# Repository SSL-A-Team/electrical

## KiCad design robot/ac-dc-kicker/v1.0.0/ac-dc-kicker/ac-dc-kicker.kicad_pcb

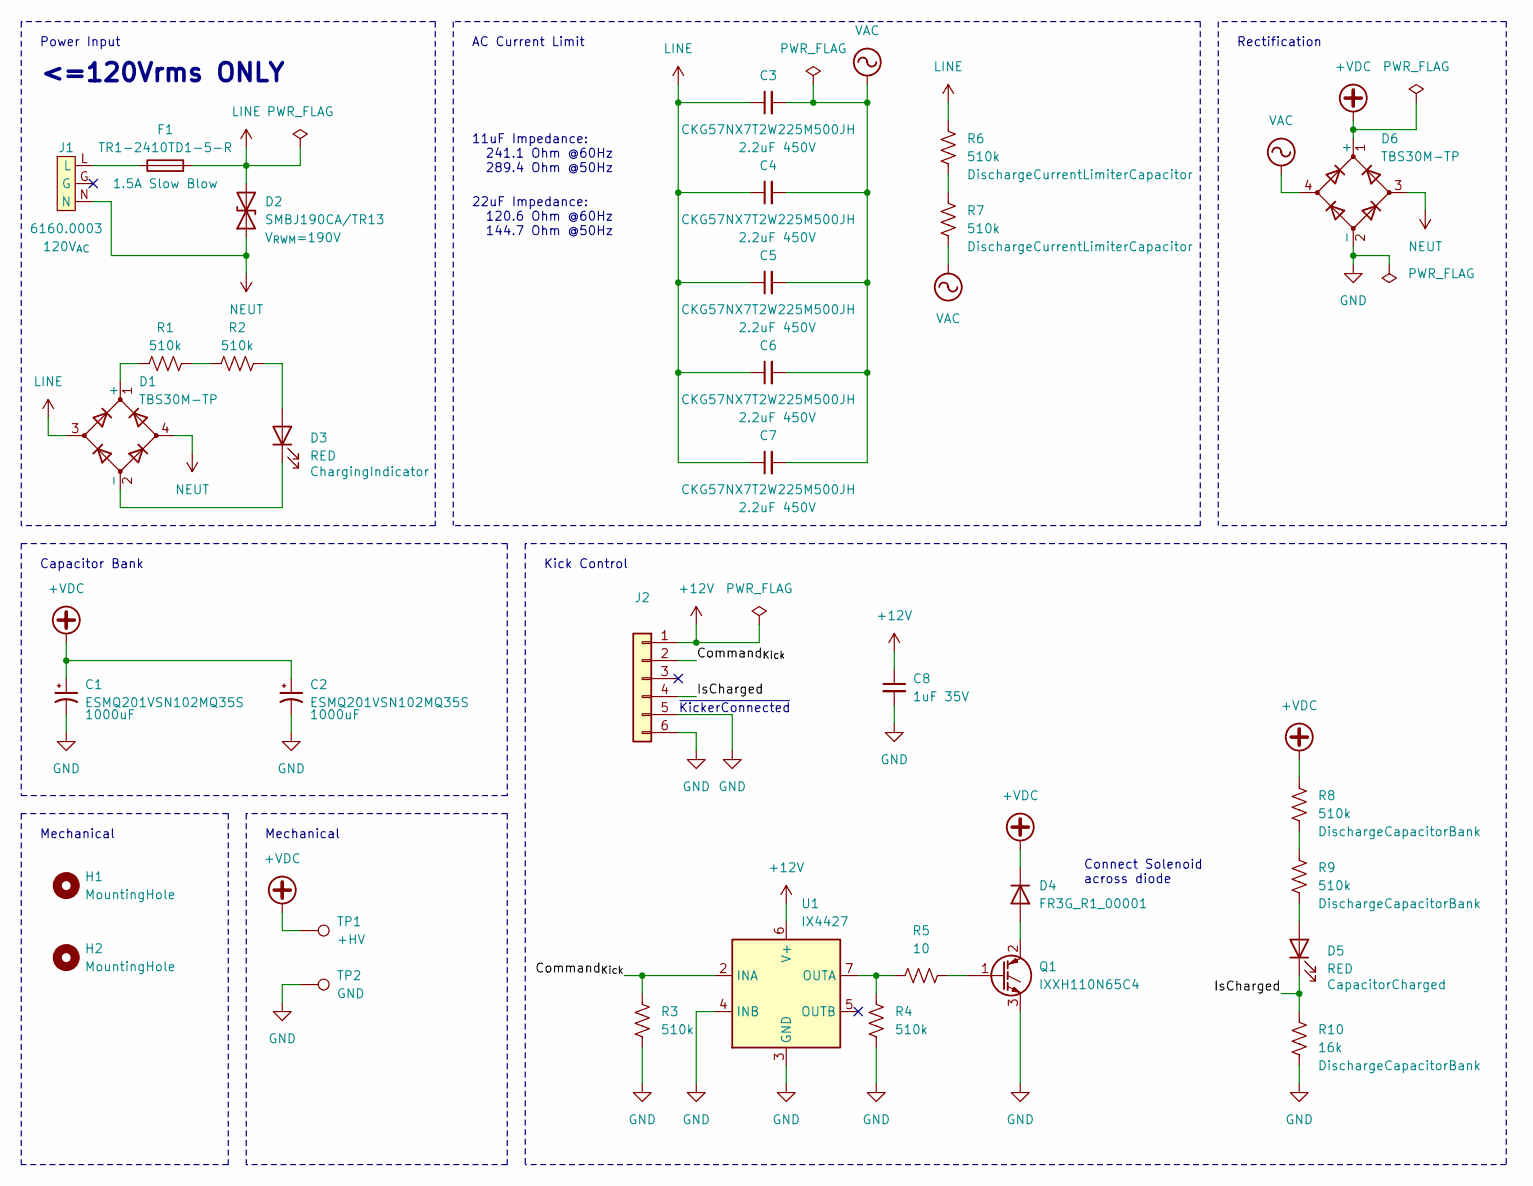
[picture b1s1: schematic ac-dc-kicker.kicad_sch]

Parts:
C1, C2: ESMQ201VSN102MQ35S; CP_Radial_D25.40mm_P10.00mm
C3, C4, C5, C6, C7: CKG57NX7T2W225M500JH; CKG57N
C8: 1uF 35V; LED_0603_1608Metric
D1, D6: TBS30M-TP; TBS
D2: SMBJ190CA/TR13; D_SMB_Non-Polar
D3, D5: RED; LED_0603_1608Metric
D4: FR3G_R1_00001; D_SMC
F1: TR1-2410TD1-5-R; Fuse_2410_6125Metric
H1, H2: MountingHole; MountingHole_3.2mm_M3
J1: 6160.0003
J2: 1x06_P2.5mm_ID0.8mm_OD2mm_TH
Q1: IXXH110N65C4; TO-247-3_Vertical
R1, R2, R3, R4, R6, R7, R8, R9: 510k; R_0805_2012Metric
R5: 10; R_0603_1608Metric
R10: 16k; R_0805_2012Metric
TP1: +HV; TestPoint_THTPad_D2.0mm_Drill1.0mm
TP2: GND; TestPoint_THTPad_D2.0mm_Drill1.0mm
U1: IX4427; SOIC-8_3.9x4.9mm_P1.27mm

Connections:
+12V: C8.1, J2.1, U1.6 (V+)
+VDC: C1.1, C2.1, D4.1 (K), D6.1 (+), R8.1, TP1.1
/Command_{Kick}: J2.2, R3.1, U1.2 (INA)
/IsCharged: D5.1 (K), J2.4, R10.1
GND: C1.2, C2.2, C8.2, D6.2 (-), J2.5, J2.6, Q1.3 (E), R3.2, R4.2, R10.2, TP2.1, U1.3 (GND), U1.4 (INB)
LINE: C3.1, C4.1, C5.1, C6.1, C7.1, D1.3, D2.2 (A2), F1.2, R6.1
NEUT: D1.4, D2.1 (A1), D6.3, J1.N
unnamed: D1.1 (+), R1.1
unnamed: D1.2 (-), D3.1 (K)
unnamed: D3.2 (A), R2.2
unnamed: D4.2 (A), Q1.2 (C)
unnamed: D5.2 (A), R9.2
unnamed: F1.1, J1.L
unnamed: Q1.1 (G), R5.2
unnamed: R1.2, R2.1
unnamed: R4.1, R5.1, U1.7 (OUTA)
unnamed: R6.2, R7.1
unnamed: R8.2, R9.1
VAC: C3.2, C4.2, C5.2, C6.2, C7.2, D6.4, R7.2

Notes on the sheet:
AC Current Limit
Power Input
<=120Vrms ONLY
Capacitor Bank
Rectification
Connect Solenoid across diode
Mechanical
22uF Impedance: 120.6 Ohm @60Hz 144.7 Ohm @50Hz
11uF Impedance: 241.1 Ohm @60Hz 289.4 Ohm @50Hz
Kick Control
~{KickerConnected}

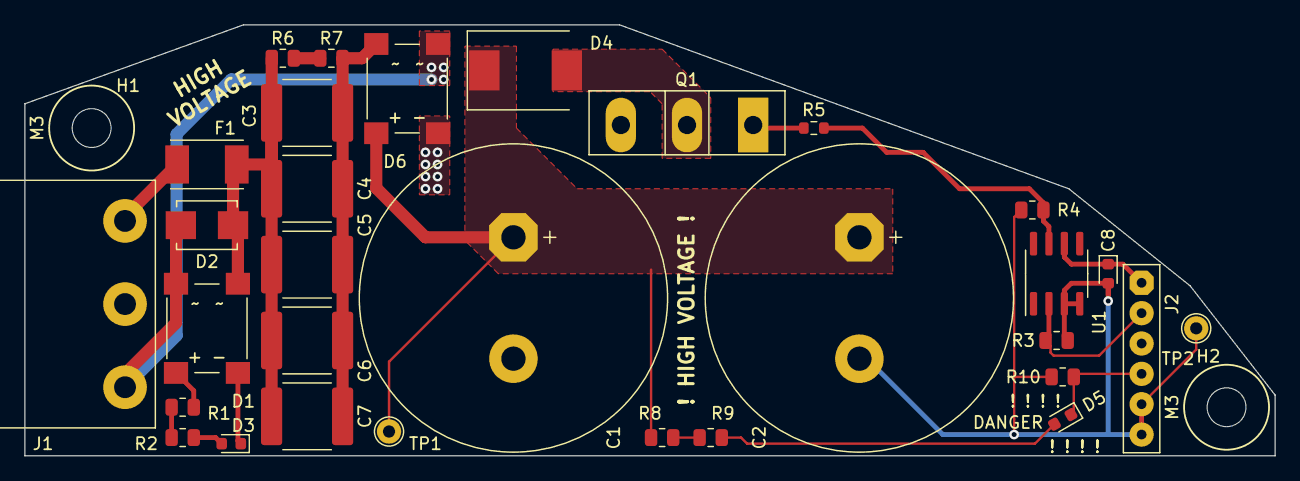
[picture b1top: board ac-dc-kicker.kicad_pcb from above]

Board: 2 copper layers, 103.0 x 35.5 mm, 33 parts (0 on the bottom side), 19 nets.

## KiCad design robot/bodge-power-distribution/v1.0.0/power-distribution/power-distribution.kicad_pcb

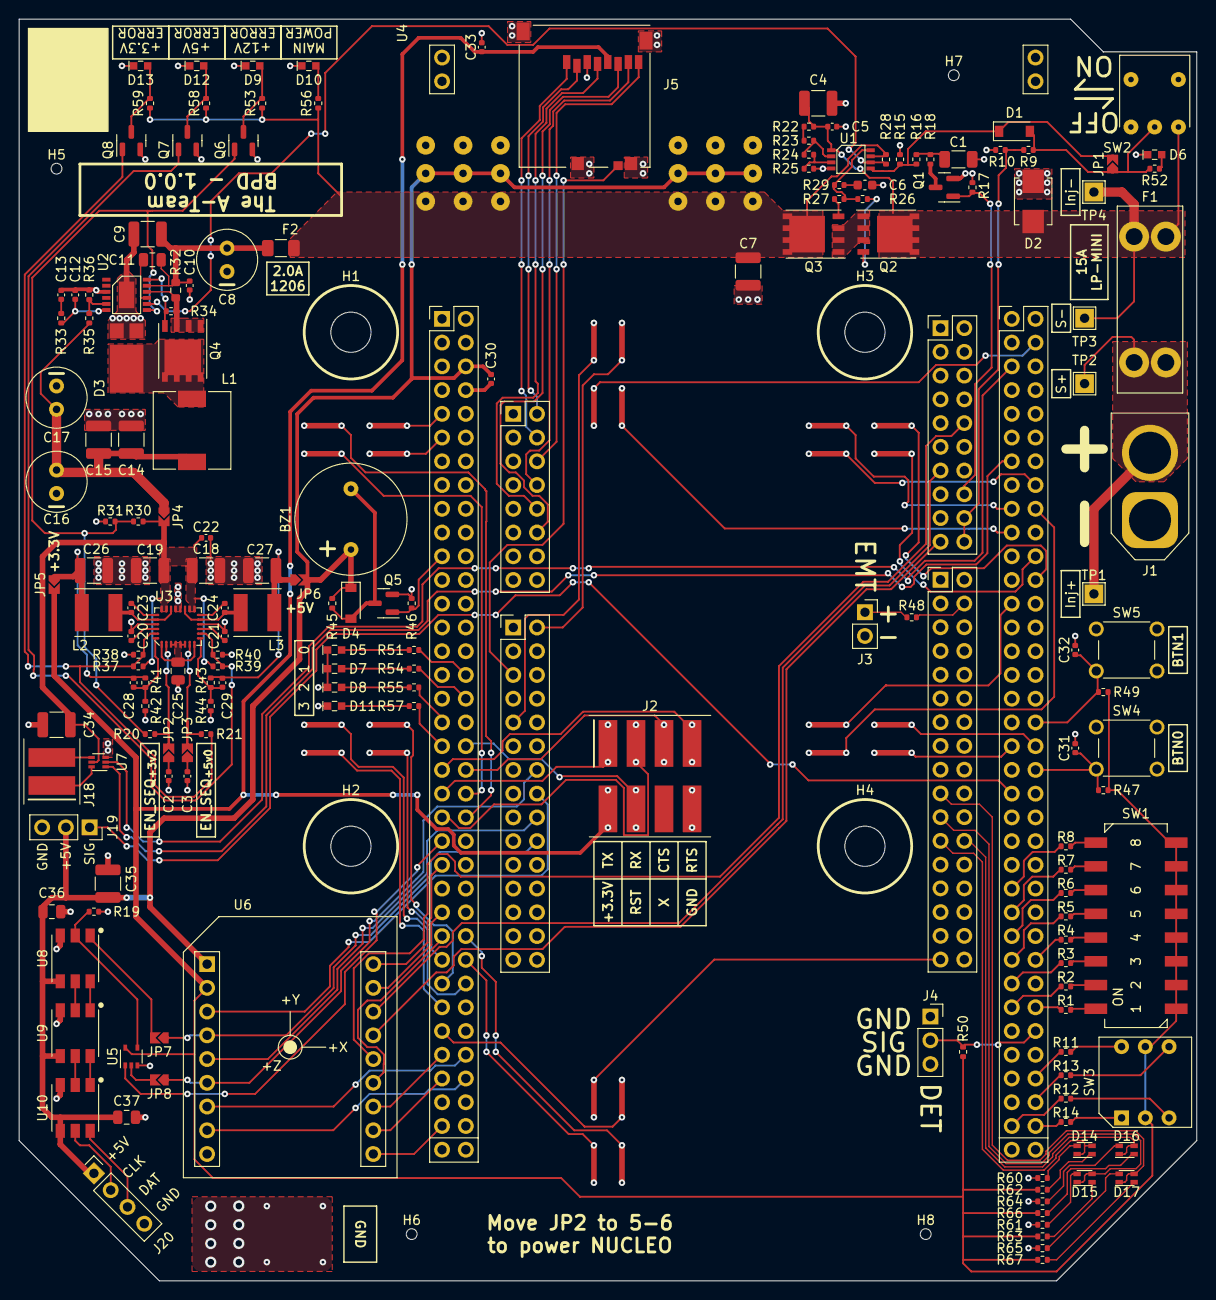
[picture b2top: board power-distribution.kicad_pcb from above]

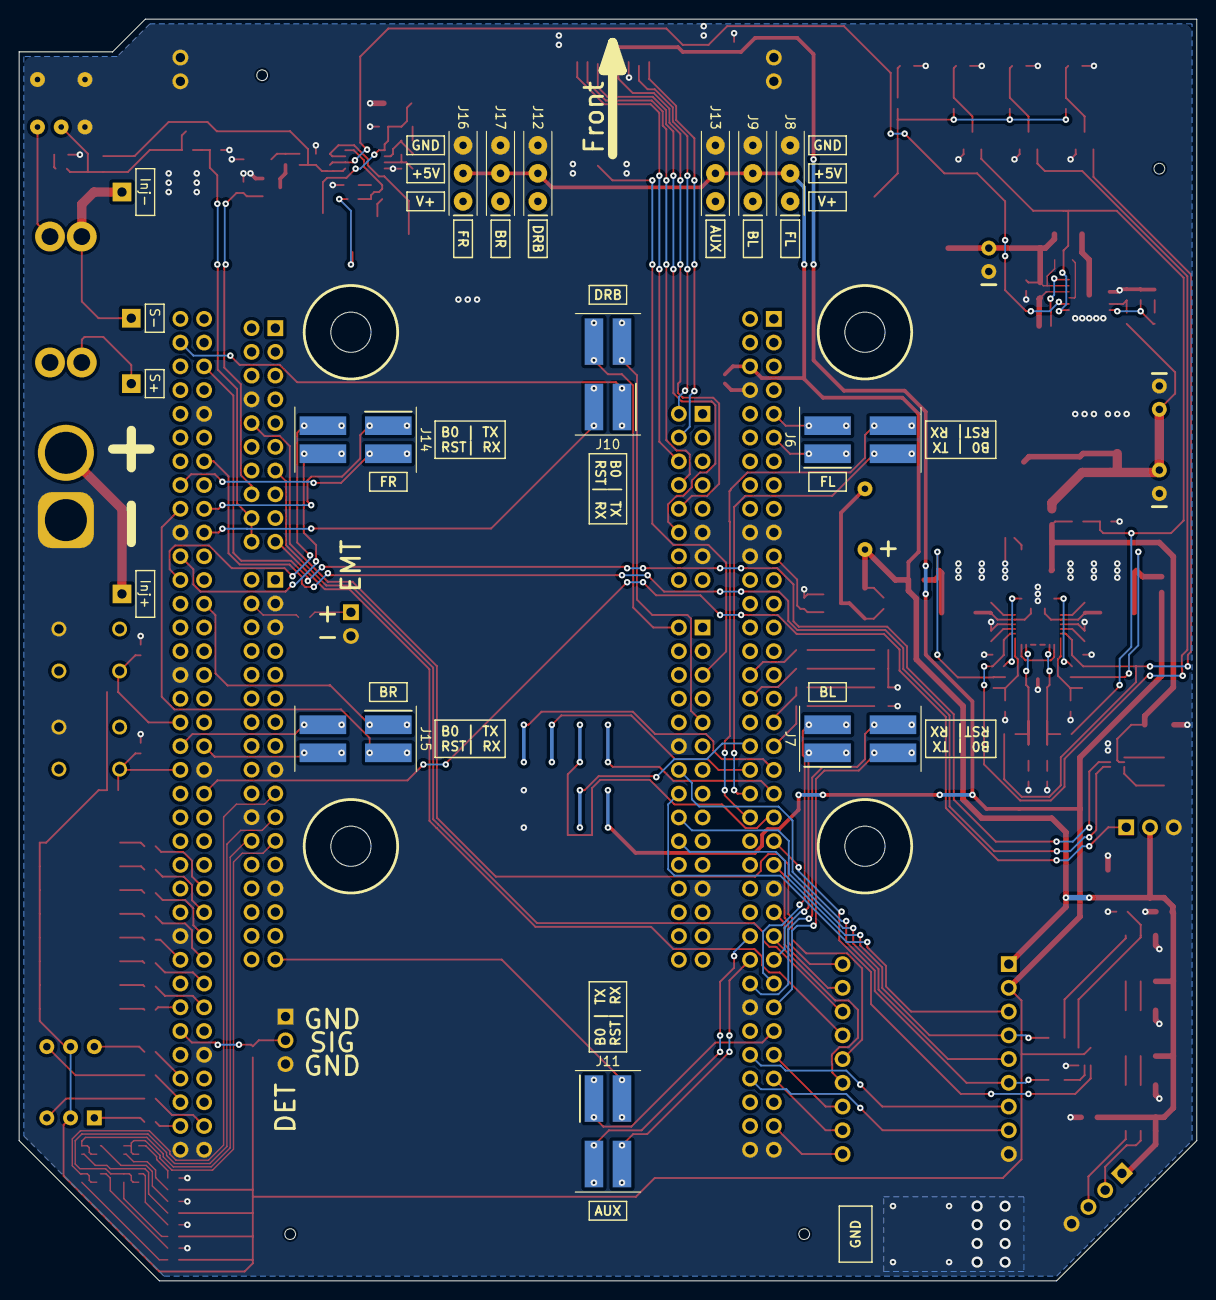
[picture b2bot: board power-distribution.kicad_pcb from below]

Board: 2 copper layers, 126.0 x 135.0 mm, 190 parts (12 on the bottom side), 171 nets.

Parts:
BZ1: AT-1224-TWT-5V-2-R
C1: 0.82uF 63V; C_1206_3216Metric
C2, C3, C5, C10, C20, C21, C22, C23, C24, C30, C31, C32, C33: 0.1uF 63V; C_0402_1005Metric
C4, C7, C9, C14, C15, C34, C35: 10uF 63V; C_1210_3225Metric
C6: 4.7nF 63V; C_0603_1608Metric
C8, C16, C17: 33uF 63V; C_Radial_D6.3mm_H11.0mm_P2.50mm
C11: 0.47uF 63V; C_0805_2012Metric
C12: 100pF 63V; C_0402_1005Metric
C13: 3300pF 63V; C_0402_1005Metric
C18, C19, C26, C27: 47uF 25V; C_1210_3225Metric
C25, C36, C37: 4.7uF 25V; C_0805_2012Metric
C28, C29: 22pF 10V; C_0402_1005Metric
D1, D4: BAT46W; D_SOD-123
D2: 824521261; D_SMB_Non-Polar
D3: SVT10100U_R1_00001; TO-277
D5, D6, D7, D8, D10, D11: Green; LED0603
D9, D12, D13: Red; LED0603
D14, D15, D16, D17: Green/Red; LED0606_CCW
F1: 15A; 3557-2
F2: 2.0A; Fuse_1206_3216Metric
H1, H2, H3, H4: MountingHole; MountingHole_4.3mm_M4
H5, H6, H7, H8: MountingHole; JLCPCB_ToolingHole_D1.152mm
J1: XT60; AMASS_XT60-M_1x02_P7.20mm_Vertical
J2: 1053082208; 2x04_P3mm_TopBottom_3x5mm_P7mm_Plug_SMD
J3: BB_{EMITTER}; PinSocket_1x02_P2.54mm_Vertical
J4: BB_{DETECTOR}; PinSocket_1x03_P2.54mm_Vertical
J5: MEM2051-00-195-00-A
J6, J7, J10, J11, J14, J15: 1053082204; 2x02_P3mm_TopBottom_3x5mm_P7mm_Plug_SMD
J8, J9, J12, J13, J16, J17: 1053072202; 1x03_P3mm_ID0.8mm_OD2mm_Plug_TH
J18: MOTOR_{BRUSHED}; 1x02_P3mm_3x5mm_Plug_SMD
J19: RS1-03-G; PinSocket_1x03_P2.54mm_Vertical
J20: ExternalDotStar; PinSocket_1x04_P2.54mm_Vertical
JP1: BYPASS_SHUTDOWN_DELAY; SolderJumper-2_2.0x1.2mm_Open
JP2: EN_SEQ_{+3v3}; SolderJumper-2_2.0x1.2mm_Open
JP3: EN_SEQ_{+5v0}; SolderJumper-2_2.0x1.2mm_Closed
JP4: SB_{+12v0}; SolderJumper-2_2.0x1.2mm_Closed
JP5: SB_{+3v3}; SolderJumper-2_2.0x1.2mm_Closed
JP6: SB_{+5v0}; SolderJumper-2_2.0x1.2mm_Closed
JP7: SB_{DSDAT}; SolderJumper-2_2.0x1.2mm_Closed
JP8: SB_{DSCLK}; SolderJumper-2_2.0x1.2mm_Closed
L1: 1217AS-H-220M=P3; DEM8045C
L2, L3: NRS5040T4R7NMGK; NRx-5040
Q1, Q5, Q6, Q7, Q8: BSS138K; SOT-23
Q2, Q3: SQJA80EP-T1_GE3; PowerPAK_SO-8L_Single
Q4: SI7465DP-T1-GE3; PowerPAK_SO-8L_Single
R1, R2, R3, R4, R5, R6, R7, R8, R11, R12, R13, R14, R50: 1k; R_0402_1005Metric
R9: 130k; R_0402_1005Metric
R10: 16k; R_0402_1005Metric
R15: 910k; R_0402_1005Metric
R16: 68k; R_0402_1005Metric
R17, R28, R34: 100k; R_0402_1005Metric
R18, R19, R42, R44, R45, R46, R47, R49, R51, R53, R54, R55, R57, R58, R59, R60, R61, R62, R63, R64, R65, R66, R67: 10k; R_0402_1005Metric
R20, R21: 82k; R_0402_1005Metric
R22: 5.1M; R_0402_1005Metric
R23: 4.3M; R_0402_1005Metric
R24: 147k; R_0402_1005Metric
R25: 154k; R_0402_1005Metric
R26, R27: 10; R_0402_1005Metric
R29: 5.1k; R_0402_1005Metric
R30, R37, R39: 54.9k; R_0402_1005Metric
R31, R38, R40: 40.2k; R_0402_1005Metric
R32: 30m 1/3W; R_0603_1608Metric
R33: 11.3k; R_0402_1005Metric
R35: 845k; R_0402_1005Metric
R36: 60.4k; R_0402_1005Metric
R41: 45.3k; R_0402_1005Metric
R43: 73.2k; R_0402_1005Metric
R48: 100; R_0402_1005Metric
R52, R56: 22k; R_0402_1005Metric
SW1: 219-8MST
SW2: CF-LD-1DC4-AR2W
SW3: 221ADC16
SW4, SW5: TS02-66-73-BK-160-SCR-D
TP1: Inject_{+}; TestPoint_THTPad_2.0x2.0mm_Drill1.0mm
TP2: Sense_{+}; TestPoint_THTPad_2.0x2.0mm_Drill1.0mm
TP3: Sense_{-}; TestPoint_THTPad_2.0x2.0mm_Drill1.0mm
TP4: Inject_{-}; TestPoint_THTPad_2.0x2.0mm_Drill1.0mm
U1: LTC4367; MS8
U2: LTC3864; MSE
U3: LTC3636; UFD_AA_NoExtraPad
U4: NUCLEO-H743ZI_MORPHO_ZIO; NUCLEO-H743ZI_MORPHO_ZIO_TH
U5: 74AHCT1G126; SOT-353_SC-70-5
U6: IMU-Breakout_1xAcc(1xSS+1xSPI+2xINT),1xIMU(2xSS+1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; MODULE_18P_22.86X27.94MM_TH
U7: DRV8220; SOT-563
U8, U9, U10: SK9822

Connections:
+3.3V: C33.1, J2.5, J5.4 (VDD), JP5.2 (B), R47.2, R49.2, R50.2, R62.2, R63.2, R66.2, R67.2, SW1.1, SW1.2, SW1.3, SW1.4, SW1.5, SW1.6, SW1.7, SW1.8, SW3.C, U5.5 (VCC), U6.2 (V_{LOGIC})
+5V: BZ1.1 (-), C30.1, C35.1, C36.2, C37.2, D4.1 (K), J8.2, J9.2, J12.2, J13.2, J16.2, J17.2, J19.2, J20.1, JP6.2 (B), R45.2, U4.CN11_6 (5V_EXT), U6.1 (5V0), U8.4 (VCC), U9.4 (VCC), U10.4 (VCC)
+12V: C18.1, C19.1, C22.1, C34.1, JP4.2 (B), R30.2, R37.2, R39.2, U3.15 (V_{IN2}), U3.16 (V_{IN2}), U3.21 (V_{IN1}), U3.22 (V_{IN1}), U7.5 (VM)
+V_{BATT(FUSED)}: C4.1, C5.1, D2.2 (A2), F1.2, Q2.5 (D), R22.1, SW2.4 (B), TP3.1, TP4.1, U1.1 (V_{IN})
+V_{BATT(PROTECTED)}: C7.1, F2.1, J8.1, J9.1, J12.1, J13.1, J16.1, J17.1, Q3.5 (D), R28.1, R53.1, R56.1, R58.1, R59.1, U1.7 (V_{OUT})
+V_{BATT(RAW)}: F1.1, J1.2, TP1.1, TP2.1
/DIP0: R8.1, U4.CN12_49 (PE12)
/DIP1: R7.1, U4.CN12_51 (PE14)
/DIP2: R6.1, U4.CN12_53 (PE15)
/DIP3: R5.1, U4.CN12_55 (PE13)
/DIP4: R4.1, U4.CN12_56 (PE11)
/DIP5: R3.1, U4.CN12_57 (PF13)
/DIP6: R2.1, U4.CN12_59 (PF12)
/DIP7: R1.1, U4.CN12_60 (PF15)
/DOTSTAR.CLK: R19.2, U5.4, U8.2 (CKI)
/DOTSTAR.DAT: JP7.2 (B), U8.1 (SDI)
/Indicators/DOTSTAR_{EXT}.CLK: J20.2, U10.5 (CKO)
/Indicators/DOTSTAR_{EXT}.DAT: J20.3, U10.6 (SDO)
/LED0: R51.1, U4.CN11_32 (PA4)
/LED1: R54.1, U4.CN11_34 (PB0)
/LED2: R55.1, U4.CN11_35 (PC2)
/LED3: R57.1, U4.CN11_37 (PC3)
/Load Switch/EN: D1.1 (K), JP1.2 (B), R15.1, R16.1, U1.5 (~SHDN)
/MCU/ACC.INT1: U4.CN11_64 (PG15), U6.7 (INT_{ACC}1)
/MCU/ACC.INT2: U4.CN11_66 (PG10), U6.8 (INT_{ACC}2)
/MCU/ACC.MISO: U4.CN9_18 (PE5), U6.5 (MISO_{ACC})
/MCU/ACC.MOSI: JP7.1 (A), U4.CN9_20 (PE6), U6.4 (MOSI_{ACC})
/MCU/ACC.SCK: JP8.1 (A), U4.CN9_14 (PE2), U6.6 (SCK_{ACC})
/MCU/ACC.~SS: U4.CN9_16 (PE4), U6.3 (~SS_{ACC})
/MCU/BB.DETECTOR: J4.2, R50.1, U4.CN12_62 (PF11)
/MCU/BB.EMITTER: R48.2, U4.CN10_4 (PE9)
/MCU/BUZZER: Q5.1 (G), R46.2, U4.CN11_21 (PB7)
/MCU/DOTSTAR.EN: U4.CN11_45 (PD7), U5.1
/MCU/IMU.INT1: U4.CN11_53 (PF0), U6.13 (INT_{IMU}1)
/MCU/IMU.INT2: U4.CN11_63 (PG9), U6.12 (INT_{IMU}2)
/MCU/IMU.INT3: U4.CN11_65 (PG12), U6.11 (INT_{IMU}3)
/MCU/IMU.INT4: U4.CN11_69 (PD9), U6.10 (INT_{IMU}4)
/MCU/IMU.MISO: U4.CN7_19 (PB4), U6.15 (MISO_{IMU})
/MCU/IMU.MOSI: U4.CN7_13 (PB5), U6.16 (MOSI_{IMU})
/MCU/IMU.SCK: U4.CN7_10 (PA5), U6.14 (SCK_{IMU})
/MCU/IMU.~SS1: U4.CN11_47 (PE3), U6.18 (~SS_{IMU1})
/MCU/IMU.~SS2: U4.CN11_51 (PF1), U6.17 (~SS_{IMU2})
/MCU/MOTOR_{AUX}.BOOT0: J11.3, U4.CN11_54 (PF8)
/MCU/MOTOR_{AUX}.RST: J11.4, U4.CN11_56 (PF9)
/MCU/MOTOR_{AUX}.RX: J11.2, U4.CN10_33 (PE0)
/MCU/MOTOR_{AUX}.TX: J11.1, U4.CN11_61 (PE1)
/MCU/MOTOR_{BL}.BOOT0: J7.3, U4.CN11_59 (PG0)
/MCU/MOTOR_{BL}.RST: J7.4, U4.CN11_58 (PG1)
/MCU/MOTOR_{BL}.RX: J7.2, U4.CN11_57 (PD0)
/MCU/MOTOR_{BL}.TX: J7.1, U4.CN11_55 (PD1)
/MCU/MOTOR_{BRUSHED}.IN1: U4.CN12_13 (PA6), U7.1 (IN1)
/MCU/MOTOR_{BRUSHED}.IN2: U4.CN12_5 (PB9), U7.2 (IN2)
/MCU/MOTOR_{BR}.BOOT0: J15.3, U4.CN12_38 (PF4)
/MCU/MOTOR_{BR}.RST: J15.4, U4.CN12_37 (PA3)
/MCU/MOTOR_{BR}.RX: J15.2, U4.CN12_18 (PB11)
/MCU/MOTOR_{BR}.TX: J15.1, U4.CN12_25 (PB10)
/MCU/MOTOR_{DRB}.BOOT0: J10.3, U4.CN9_9 (PC2)
/MCU/MOTOR_{DRB}.RST: J10.4, U4.CN9_2 (PD7)
/MCU/MOTOR_{DRB}.RX: J10.2, U4.CN12_19 (PC7)
/MCU/MOTOR_{DRB}.TX: J10.1, U4.CN12_4 (PC6)
/MCU/MOTOR_{FL}.BOOT0: J6.3, U4.CN11_42 (PG2)
/MCU/MOTOR_{FL}.RST: J6.4, U4.CN11_44 (PG3)
/MCU/MOTOR_{FL}.RX: J6.2, U4.CN11_9 (PF6)
/MCU/MOTOR_{FL}.TX: J6.1, U4.CN11_11 (PF7)
/MCU/MOTOR_{FR}.BOOT0: J14.3, U4.CN12_24 (PB1)
/MCU/MOTOR_{FR}.RST: J14.4, U4.CN12_22 (PB2)
/MCU/MOTOR_{FR}.RX: J14.2, U4.CN12_16 (PB12)
/MCU/MOTOR_{FR}.TX: J14.1, U4.CN12_17 (PB6)
/MCU/MOTOR_{SERVO}.SIG: J19.1, U4.CN12_41 (PD13)
/MCU/RADIO.CTS: J2.3, U4.CN11_40 (PD3)
/MCU/RADIO.RST: J2.6, U4.CN11_38 (PC0)
/MCU/RADIO.RTS: J2.4, U4.CN11_39 (PD4)
/MCU/RADIO.RX: J2.2, U4.CN11_43 (PD6)
/MCU/RADIO.TX: J2.1, U4.CN11_41 (PD5)
/MCU/SDMMC.CK: J5.5 (CLK), U4.CN8_10 (PC12)
/MCU/SDMMC.CMD: J5.3 (CMD), U4.CN8_12 (PD2)
/MCU/SDMMC.D0: J5.7 (DAT0), U4.CN8_2 (PC8)
/MCU/SDMMC.D1: J5.8 (DAT1), U4.CN8_4 (PC9)
/MCU/SDMMC.D2: J5.1 (DAT2), U4.CN8_6 (PC10)
/MCU/SDMMC.D3: J5.2 (CD/DAT3), U4.CN8_8 (PC11)
/MCU/~BTN0: C31.1, R47.1, SW4.2, U4.CN12_40 (PE8)
/MCU/~BTN1: C32.1, R49.1, SW5.2, U4.CN12_36 (PF5)
/MCU/~SDCardDetect: J5.~{CD}, U4.CN9_5 (PC3)
/PGOOD_{3v3}: Q8.1 (G), R21.2, R37.1, R38.2, U3.27 (PGOOD1)
/PGOOD_{5v0}: Q7.1 (G), R39.1, R40.2, U3.10 (PGOOD2)
/PGOOD_{12v0}: Q6.1 (G), R20.2, R30.1, R31.2, U2.7 (PGOOD)
/PGOOD_{VBATT}: R28.2, U1.6 (~FAULT), U2.8 (RUN)
/PowerSwitchState: R9.1, R10.2, U4.CN7_18 (PD15), U4.CN7_20 (PF3)
/Regulator 3v3 & 5v0/EN_{3v3}: JP2.2 (B), R20.1, U3.2 (RUN1)
/Regulator 3v3 & 5v0/EN_{5v0}: JP3.2 (B), R21.1, U3.7 (RUN2)
/Regulator 3v3 & 5v0/FB_{3v3}: C28.2, R41.2, R42.1, U3.28 (V_{FB1})
/Regulator 3v3 & 5v0/FB_{5v0}: C29.2, R43.2, R44.1, U3.9 (V_{FB2})
/Regulator 3v3 & 5v0/INTV_{CC}: C25.1, U3.1 (ITH1), U3.3 (MODE/SYNC), U3.4 (RT), U3.5 (INTV_{CC}), U3.6 (TMON), U3.8 (ITH2)
/Regulator 3v3 & 5v0/SW_{3v3}: C23.2, L2.1, U3.20 (SW1), U3.24 (SW1)
/Regulator 3v3 & 5v0/SW_{5v0}: C24.2, L3.1, U3.13 (SW2), U3.17 (SW2)
/Regulator 12v0/V_{SENSE+}: C8.1, C9.1, C10.1, C11.1, F2.2, R32.1, U2.11 (V_{IN})
/Regulator 12v0/V_{SENSE-}: Q4.1 (S), Q4.2 (S), Q4.3 (S), R32.2, R34.1, U2.10 (SENSE)
/RobotID0: R14.1, U4.CN12_70 (PG6)
/RobotID1: R13.1, U4.CN12_68 (PG5)
/RobotID2: R12.1, U4.CN12_69 (PG4)
/RobotID3: R11.1, U4.CN12_66 (PG8)
/RobotID.BL: D15.1 (K1), D15.3 (A2), U4.CN10_21 (PD12)
/RobotID.BR: D17.1 (K1), D17.3 (A2), U4.CN10_19 (PD13)
/RobotID.FL: D14.1 (K1), D14.3 (A2), U4.CN10_23 (PD11)
/RobotID.FR: D16.1 (K1), D16.3 (A2), U4.CN10_24 (PE10)
/ShutdownComplete: Q1.1 (G), R17.1, U4.CN7_16 (PD14)
/V_{Switch}: D1.2 (A), JP1.1 (A), R9.2, R52.1, SW2.5 (COM)
GND: C1.2, C2.2, C3.2, C4.2, C5.2, C6.2, C7.2, C8.2, C9.2, C10.2, C12.2, C13.2, C14.2, C15.2, C16.2, C17.2, C18.2, C19.2, C20.2, C21.2, C22.2, C25.2, C26.2, C27.2, C30.2, C31.2, C32.2, C33.2, C34.2, C35.2, C36.1, C37.1, D2.1 (A1), D3.1 (A), D3.2 (A), D5.1 (K), D6.1 (K), D7.1 (K), D8.1 (K), D9.1 (K), D10.1 (K), D11.1 (K), D12.1 (K), D13.1 (K), J1.1, J2.8, J3.2, J4.1, J4.3, J5.6 (VSS), J5.9 (Anchor), J8.3, J9.3, J12.3, J13.3, J16.3, J17.3, J19.3, J20.4, Q1.2 (S), Q5.2 (S), Q6.2 (S), Q7.2 (S), Q8.2 (S), R10.1, R15.2, R17.2, R19.1, R25.1, R31.1, R36.2, R38.1, R40.1, R42.2, R44.2, R46.1, R60.1, R61.1, R64.1, R65.1, SW2.1, SW2.3, SW2.6 (A), SW4.3, SW5.3, U1.4 (GND), U2.3 (SGND), U2.13 (PGND), U3.12 (GND), U3.18 (GND), U3.19 (GND), U3.25 (GND), U4.CN3_1 (GND), U4.CN3_2 (GND), U4.CN4_1 (GND), U4.CN4_2 (GND), U4.CN7_8 (GND), U4.CN8_11 (GND), U4.CN8_13 (GND), U4.CN9_12 (GND), U4.CN9_23 (GND), U4.CN10_3 (AGND), U4.CN10_5 (GND), U4.CN10_17 (GND), U4.CN10_22 (GND), U4.CN10_27 (GND), U4.CN11_8 (GND), U4.CN11_19 (GND), U4.CN11_20 (GND), U4.CN11_22 (GND), U4.CN11_49 (GND), U4.CN11_60 (GND), U4.CN12_9 (GND), U4.CN12_20 (GND), U4.CN12_32 (AGND), U4.CN12_39 (GND), U4.CN12_54 (GND), U4.CN12_63 (GND), U4.CN15_1 (GND), U4.CN15_2 (GND), U4.CN16_1 (GND), U4.CN16_2 (GND), U5.3 (GND), U6.9 (GND), U7.3 (GND), U8.3 (GND), U9.3 (GND), U10.3 (GND)
unnamed: BZ1.2 (+), D4.2 (A), Q5.3 (D), R45.1
unnamed: C1.1, R16.2, R18.1
unnamed: C2.1, JP2.1 (A)
unnamed: C3.1, JP3.1 (A)
unnamed: C6.1, R29.2
unnamed: C11.2, U2.9 (CAP)
unnamed: C12.1, R33.2, U2.6 (ITH)
unnamed: C13.1, R33.1
unnamed: C14.1, C15.1, C16.1, C17.1, JP4.1 (A), L1.2, R35.1
unnamed: C20.1, U3.26 (TRACKSS1)
unnamed: C21.1, U3.11 (TRACKSS2)
unnamed: C23.1, U3.23 (BOOST1)
unnamed: C24.1, U3.14 (BOOST2)
unnamed: C26.1, C28.1, JP5.1 (A), L2.2, R41.1
unnamed: C27.1, C29.1, JP6.1 (A), L3.2, R43.1
unnamed: D3.3 (K), L1.1, Q4.5 (D)
unnamed: D5.2 (A), R51.2
unnamed: D6.2 (A), R52.2
unnamed: D7.2 (A), R54.2
unnamed: D8.2 (A), R55.2
unnamed: D9.2 (A), Q6.3 (D), R53.2
unnamed: D10.2 (A), R56.2
unnamed: D11.2 (A), R57.2
unnamed: D12.2 (A), Q7.3 (D), R58.2
unnamed: D13.2 (A), Q8.3 (D), R59.2
unnamed: D14.2 (A1), R62.1
unnamed: D14.4 (K2), R60.2
unnamed: D15.2 (A1), R63.1
unnamed: D15.4 (K2), R61.2
unnamed: D16.2 (A1), R66.1
unnamed: D16.4 (K2), R64.2
unnamed: D17.2 (A1), R67.1
unnamed: D17.4 (K2), R65.2
unnamed: J3.1, R48.1
unnamed: J18.1, U7.6 (OUT1)
unnamed: J18.2, U7.4 (OUT2)
unnamed: JP8.2 (B), U5.2
unnamed: Q1.3 (D), R18.2
unnamed: Q2.1 (S), Q2.2 (S), Q2.3 (S), Q3.1 (S), Q3.2 (S), Q3.3 (S)
unnamed: Q2.4 (G), R26.1
unnamed: Q3.4 (G), R27.2
unnamed: Q4.4 (G), R34.2, U2.12 (GATE)
unnamed: R1.2, SW1.16
unnamed: R2.2, SW1.15
unnamed: R3.2, SW1.14
unnamed: R4.2, SW1.13
unnamed: R5.2, SW1.12
unnamed: R6.2, SW1.11
unnamed: R7.2, SW1.10
unnamed: R8.2, SW1.9
unnamed: R11.2, SW3.6 (8)
unnamed: R12.2, SW3.3 (4)
unnamed: R13.2, SW3.4 (2)
unnamed: R14.2, SW3.1
unnamed: R22.2, R23.1
unnamed: R23.2, R24.1, U1.2 (UV)
unnamed: R24.2, R25.2, U1.3 (OV)
unnamed: R26.2, R27.1, R29.1, U1.8 (GATE)
unnamed: R35.2, R36.1, U2.5 (V_{FB})
unnamed: U8.5 (CKO), U9.2 (CKI)
unnamed: U8.6 (SDO), U9.1 (SDI)
unnamed: U9.6 (SDO), U10.1 (SDI)
unnamed: U9.5 (CKO), U10.2 (CKI)

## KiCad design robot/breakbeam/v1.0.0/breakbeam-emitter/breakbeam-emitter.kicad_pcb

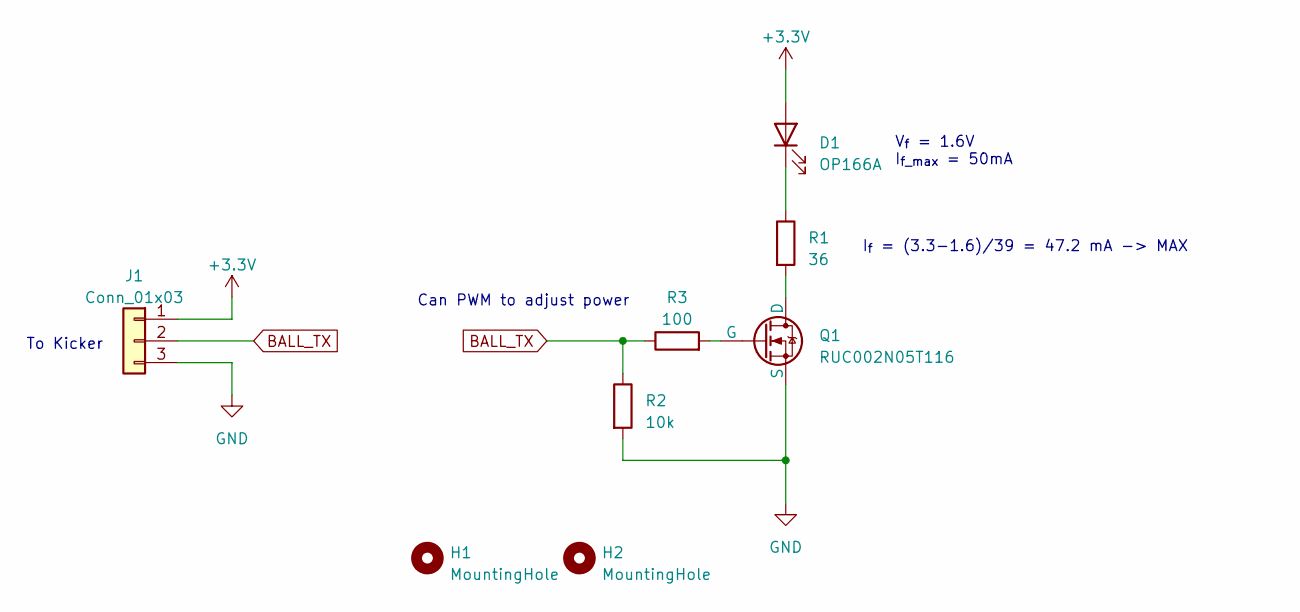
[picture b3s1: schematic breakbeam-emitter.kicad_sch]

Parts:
D1: OP166A; LED_D3.0mm
H1, H2: MountingHole; MountingHole_2.2mm_M2
J1: Conn_01x03; JST_SH_SM03B-SRSS-TB_1x03-1MP_P1.00mm_Horizontal
Q1: RUC002N05T116; SOT23-3_ROM-L
R1: 36; R_0603_1608Metric_Pad0.98x0.95mm_HandSolder
R2: 10k; R_0603_1608Metric_Pad0.98x0.95mm_HandSolder
R3: 100; R_0603_1608Metric_Pad0.98x0.95mm_HandSolder

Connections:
+3.3V: D1.2 (A), J1.1
BALL_TX: J1.2, R2.1, R3.1
GND: J1.3, Q1.3 (S), R2.2
unnamed: D1.1 (K), R1.1
unnamed: Q1.1 (D), R1.2
unnamed: Q1.2 (G), R3.2

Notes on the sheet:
I_{f} = (3.3-1.6)/39 = 47.2 mA -> MAX
To Kicker
V_{f} = 1.6V I_{f_max} = 50mA
Can PWM to adjust power

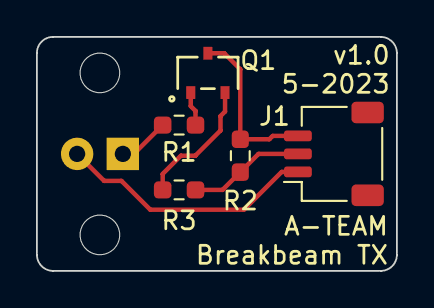
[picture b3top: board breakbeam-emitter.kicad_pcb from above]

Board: 2 copper layers, 20.0 x 13.0 mm, 8 parts (1 on the bottom side), 6 nets.

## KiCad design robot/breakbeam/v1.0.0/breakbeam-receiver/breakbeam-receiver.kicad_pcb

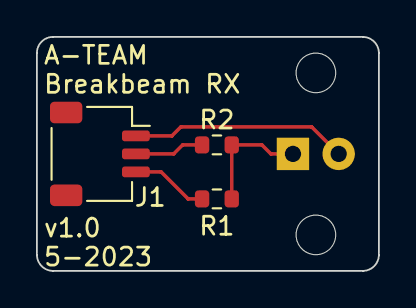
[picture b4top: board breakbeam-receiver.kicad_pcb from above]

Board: 2 copper layers, 19.0 x 13.0 mm, 6 parts (1 on the bottom side), 4 nets.

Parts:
H1, H2: MountingHole; MountingHole_2.2mm_M2
J1: Conn_01x03; JST_SH_SM03B-SRSS-TB_1x03-1MP_P1.00mm_Horizontal
Q1: OP506B; LED_D3.0mm
R1: 2k; R_0603_1608Metric
R2: 100; R_0603_1608Metric

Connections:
+3.3V: J1.1, Q1.2 (C)
BALL_RX: J1.2, R2.2
GND: J1.3, R1.2
unnamed: Q1.1 (E), R1.1, R2.1
